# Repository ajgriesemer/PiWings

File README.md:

# PiWings
A shield for connecting an XBee to a Raspberry Pi over the Pi's GPIO UART. The board also includes pads for optional LEDs connected to the RSSI, Assoc and Power LEDs from the XBee.

RPiXBee.brd and RPiXBee.sch are the board layout files that are compatible with Eagle 7.6.0

BOM.csv is an output file from DigiKey.com showing a typical parts list.

e14_Rpi3_RevA.lbr is Element 14's Raspberry Pi 3 library that provides the Raspberry Pi header, hole locations and silkscreen. I removed the Raspberry Pi silkscreen from the library.

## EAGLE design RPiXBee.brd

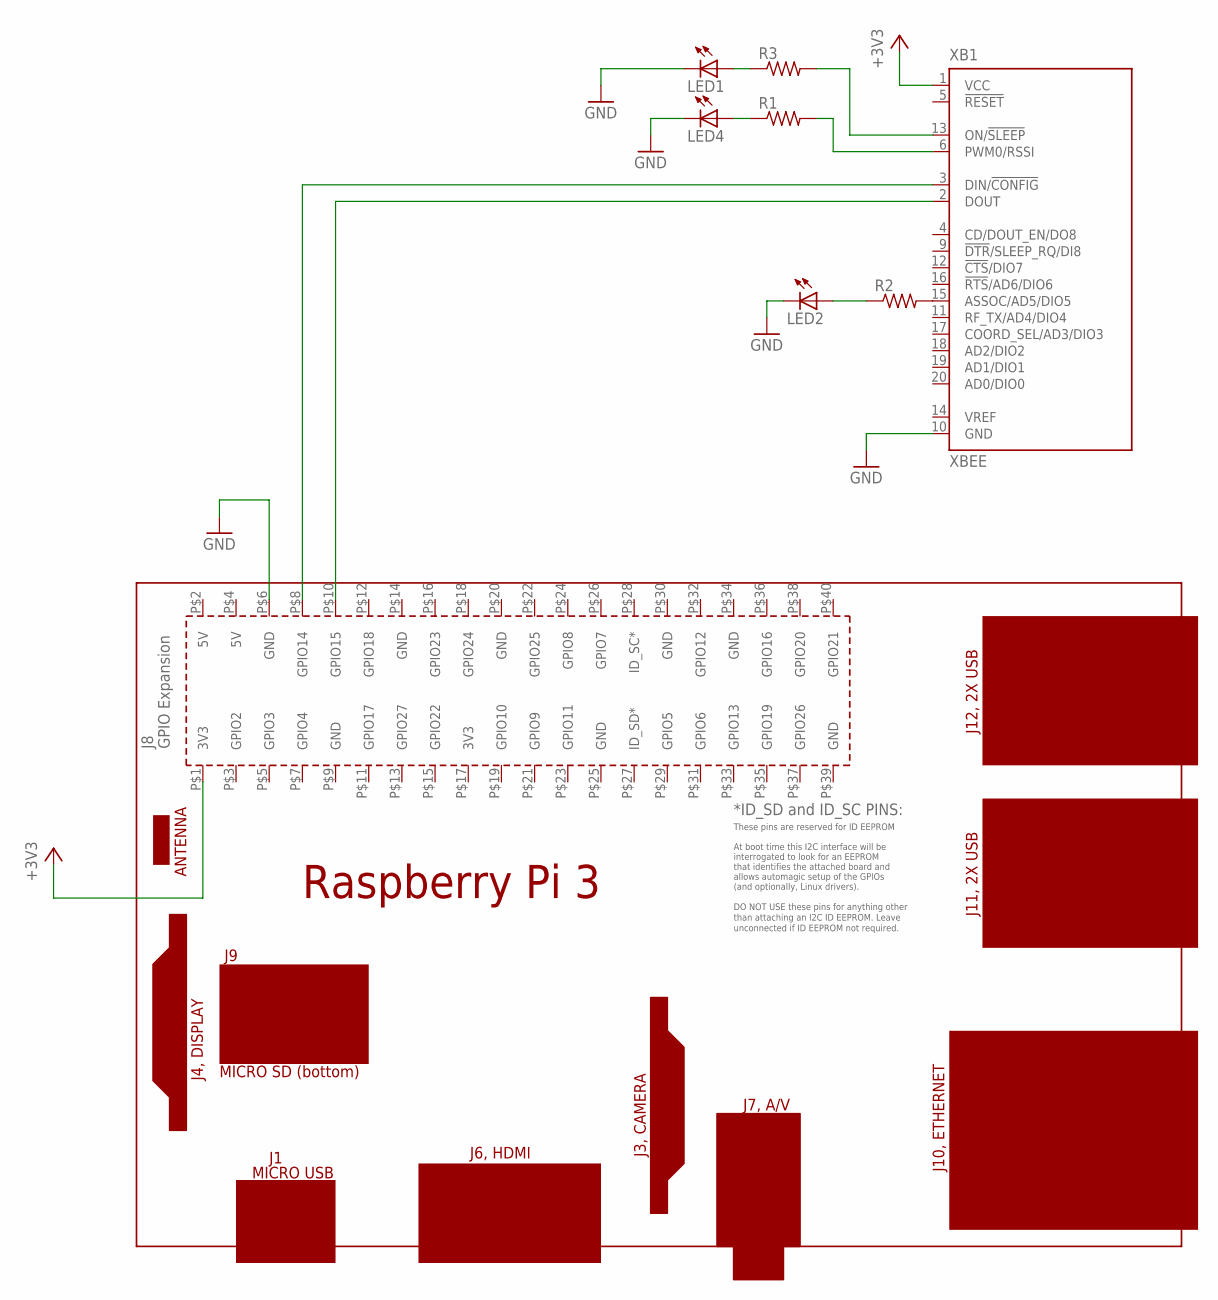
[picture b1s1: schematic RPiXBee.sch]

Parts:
LED1, LED2, LED4: LEDCHIP-LED0603; CHIP-LED0603
PCB1: RPI3NO-CONNECTORS; RPI3-NO-CONNECTORS
R1, R2, R3: R-US_R0603; R0603
XB1: XBEE

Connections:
+3V3: PCB1.P$1 (3V3), XB1.1 (VCC)
GND: LED1.C, LED2.C, LED4.C, PCB1.P$6 (GND), XB1.10 (GND)
unnamed: R1.2, XB1.6 (PWM0/RSSI)
unnamed: R2.2, XB1.15 (ASSOC/AD5/DIO5)
unnamed: LED4.A, R1.1
unnamed: R3.2, XB1.13 (ON/!SLEEP)
unnamed: LED1.A, R3.1
unnamed: LED2.A, R2.1
RPIRX-XBEEDOUT: PCB1.P$10 (GPIO15), XB1.2 (DOUT)
RPITX-XBEEDIN: PCB1.P$8 (GPIO14), XB1.3 (DIN/!CONFIG)

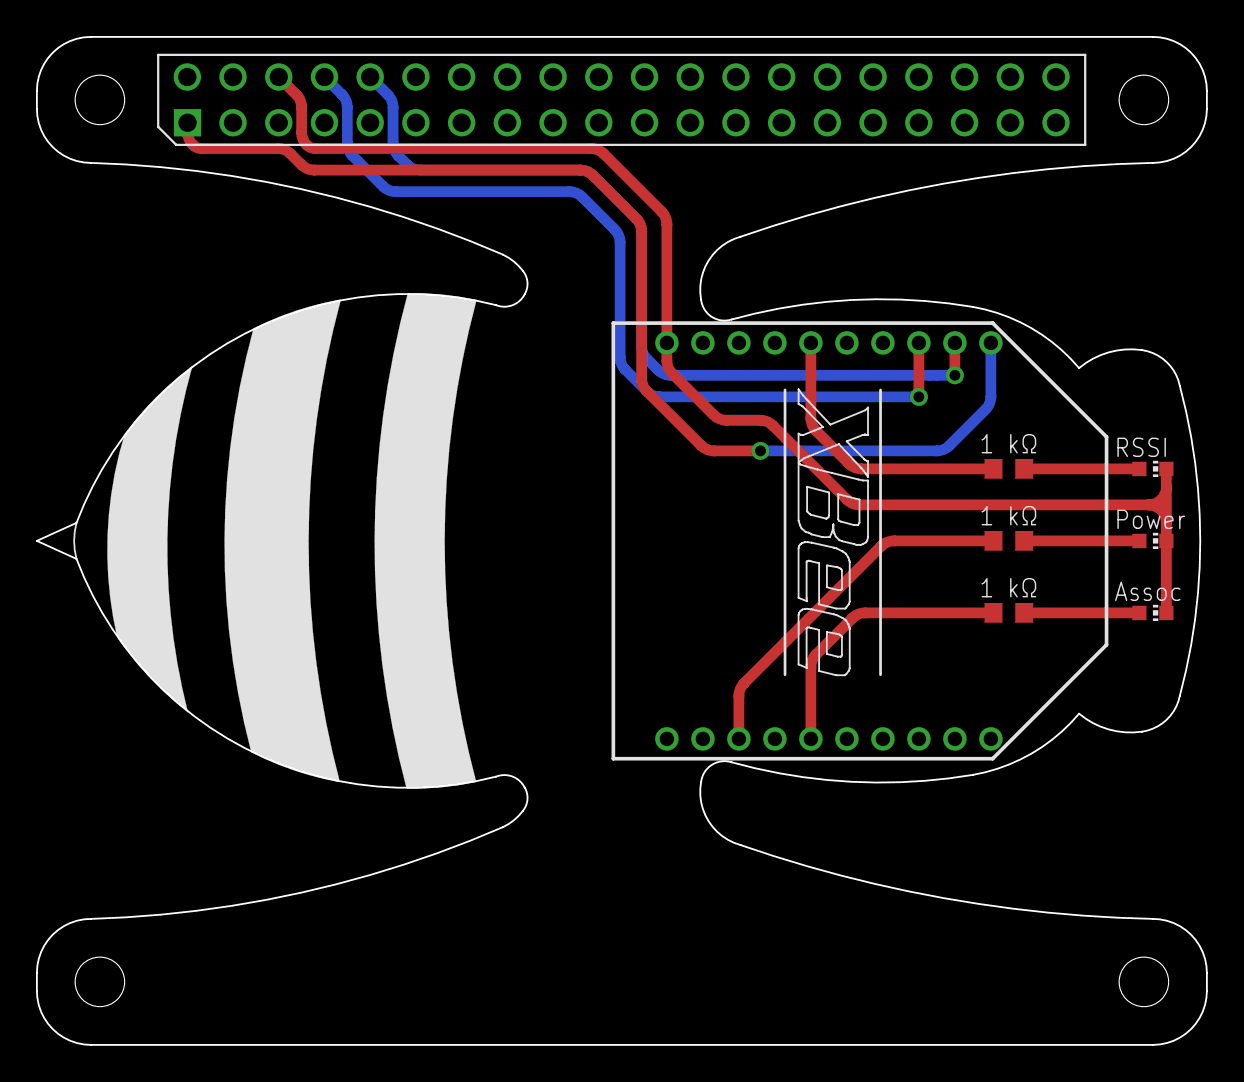
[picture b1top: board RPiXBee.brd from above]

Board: 2 copper layers, 65.0 x 56.0 mm, 8 parts (0 on the bottom side), 10 nets.

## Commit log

2017-05-10 Initial commit of eagles files.
2017-05-16 Added BOM.
2017-05-16 Added readme
